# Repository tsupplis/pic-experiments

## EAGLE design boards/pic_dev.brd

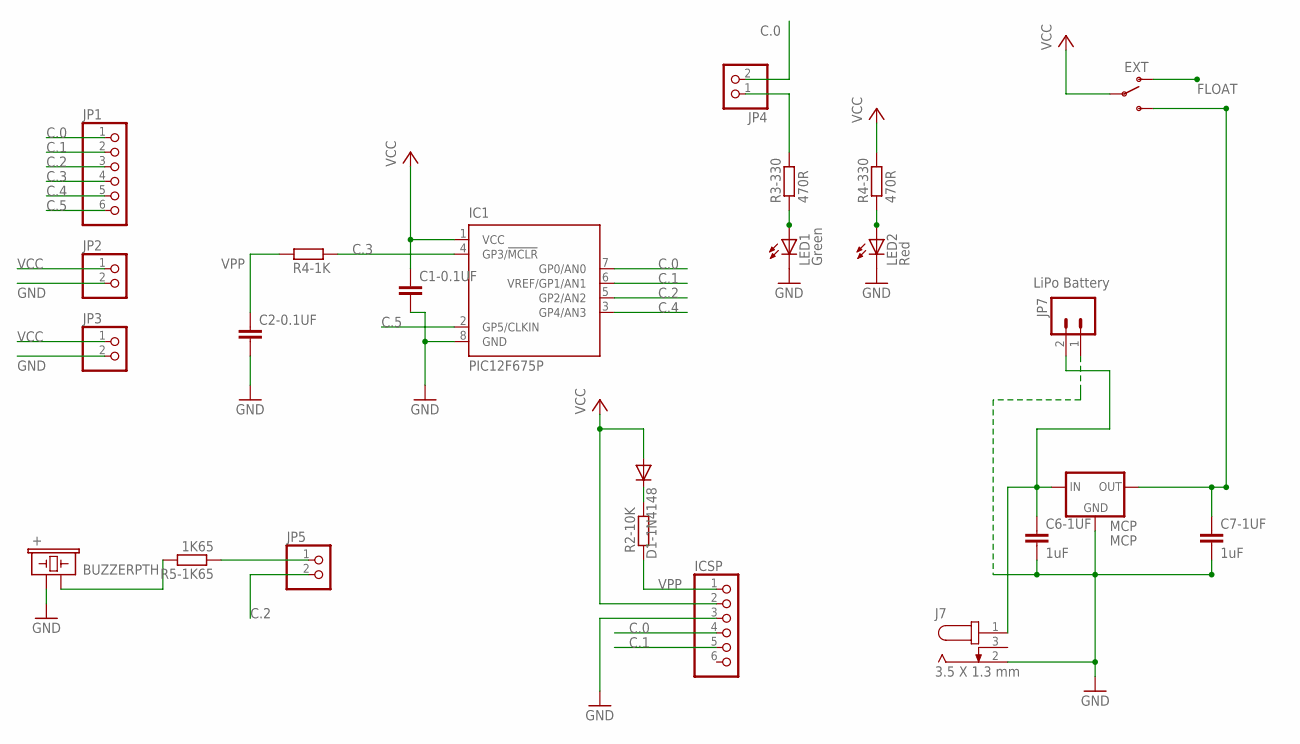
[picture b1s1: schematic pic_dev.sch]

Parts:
+: BUZZERPTH; BUZZER-12MM
C1-0.1UF, C2-0.1UF: C-EU025-025X050; C025-025X050
C6-1UF, C7-1UF: 1uF; C050-025X075
D1-1N4148: 1N4148; DO35-7
IC1: PIC12F675P; DIL8
ICSP: PINHD-1X6; 1X06
J7: 3.5 X 1.3 mm; 3.5X1.3MM_DC_JACK
JP1: PINHD-1X6; 1X06
JP2, JP3, JP4, JP5: PINHD-1X2; 1X02
JP7: LiPo Battery; JST-2-PTH
LED1: Green; LED3MM
LED2: Red; LED3MM
MCP: MCP; TO92-
ON: EXT; SWITCH-SPDT
R2-10K, R4-1K: R-EU_0207/10; 0207/10
R3-330, R4-330: 470R; 0207/10
R5-1K65: 1K65; 0207/10

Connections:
C.0: IC1.7 (GP0/AN0), ICSP.4, JP1.1, JP4.2
C.1: IC1.6 (VREF/GP1/AN1), ICSP.5, JP1.2
C.2: IC1.5 (GP2/AN2), JP1.3, JP5.2
C.3: IC1.4 (GP3/!MCLR), JP1.4, R4-1K.1
C.4: IC1.3 (GP4/AN3), JP1.5
C.5: IC1.2 (GP5/CLKIN), JP1.6
FLOAT: ON.1 (O)
GND: +.+ (1), C1-0.1UF.2, C2-0.1UF.2, C6-1UF.2, C7-1UF.2, IC1.8 (GND), ICSP.3, J7.2, JP2.2, JP3.2, JP7.1, LED1.K (C), LED2.K (C), MCP.3 (GND)
unnamed: LED2.A, R4-330.1
unnamed: +.- (2), R5-1K65.2
unnamed: JP4.1, R3-330.2
unnamed: LED1.A, R3-330.1
unnamed: D1-1N4148.C, R2-10K.2
unnamed: JP5.1, R5-1K65.1
VCC: C1-0.1UF.1, D1-1N4148.A, IC1.1 (VCC), ICSP.2, JP2.1, JP3.1, ON.2, R4-330.2
VCCEXT: C6-1UF.1, J7.1, JP7.2, MCP.2 (IN)
VCCREG: C7-1UF.1, MCP.1 (OUT), ON.3 (S)
VPP: C2-0.1UF.1, ICSP.1, R2-10K.1, R4-1K.2

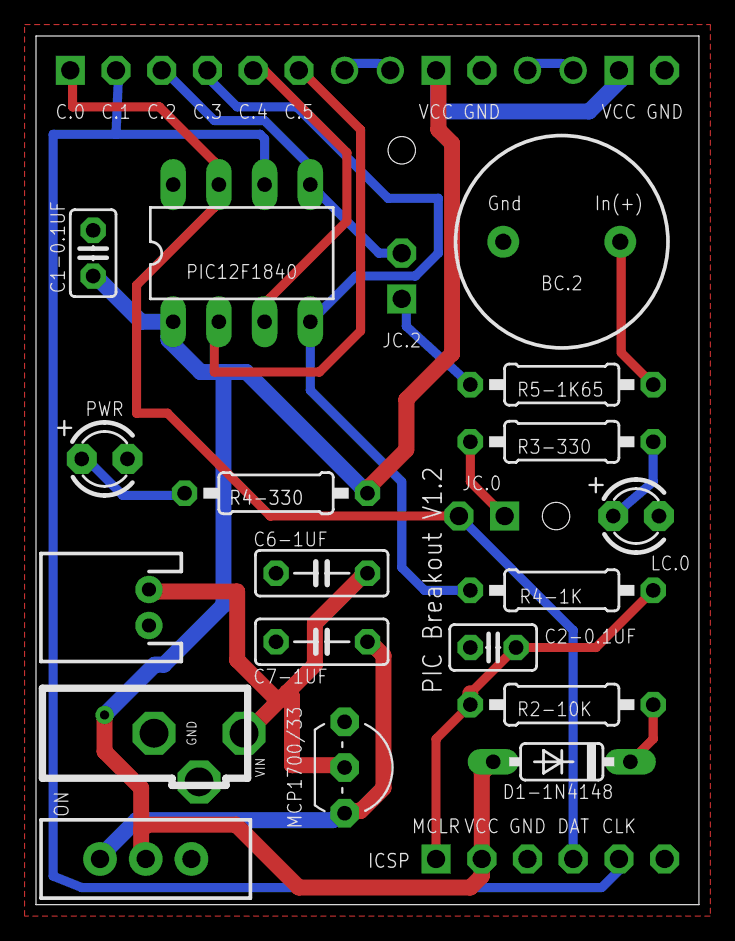
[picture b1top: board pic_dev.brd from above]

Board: 2 copper layers, 36.8 x 48.3 mm, 24 parts (0 on the bottom side), 17 nets.

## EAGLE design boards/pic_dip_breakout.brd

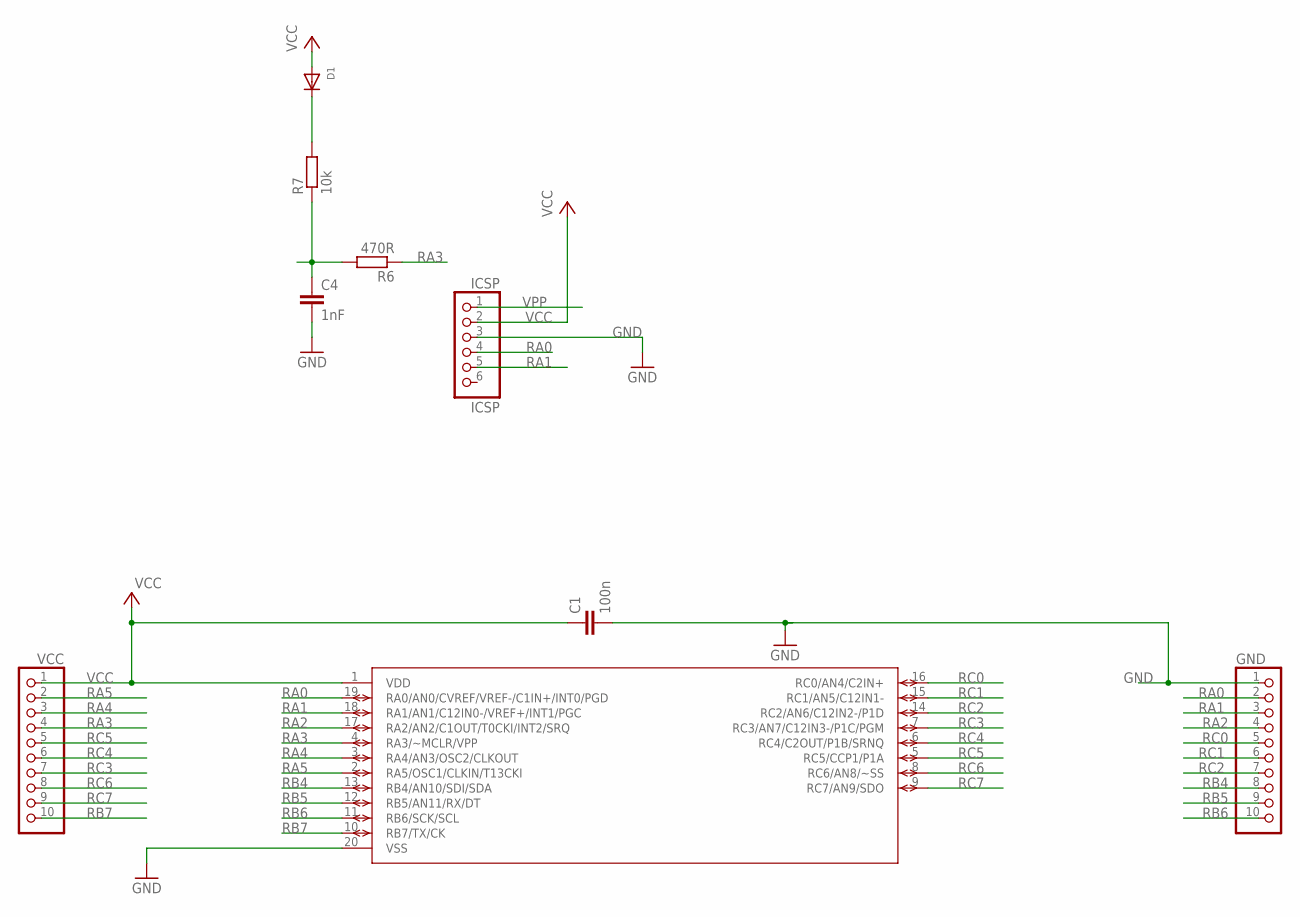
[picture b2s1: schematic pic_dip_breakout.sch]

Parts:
C1: 100n; C0805
C4: 1nF; C0805
D1: DIODESOD-323F; SOD-323F
GND: PH1X10OCT076; PH1X10OCT76
ICSP: ICSP; 1X06
R6: 470R; R0805
R7: 10k; R0805
U$1: PIC18F14K22-I/P; DIP254P762X533-20
VCC: PH1X10OCT076; PH1X10OCT76

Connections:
GND: C1.2, C4.2, GND.1, ICSP.3, U$1.20 (VSS)
unnamed: D1.C, R7.2
RA0: GND.2, ICSP.4, U$1.19 (RA0/AN0/CVREF/VREF-/C1IN+/INT0/PGD)
RA1: GND.3, ICSP.5, U$1.18 (RA1/AN1/C12IN0-/VREF+/INT1/PGC)
RA2: GND.4, U$1.17 (RA2/AN2/C1OUT/T0CKI/INT2/SRQ)
RA3: R6.1, U$1.4 (RA3/~MCLR/VPP), VCC.4
RA4: U$1.3 (RA4/AN3/OSC2/CLKOUT), VCC.3
RA5: U$1.2 (RA5/OSC1/CLKIN/T13CKI), VCC.2
RB4: GND.8, U$1.13 (RB4/AN10/SDI/SDA)
RB5: GND.9, U$1.12 (RB5/AN11/RX/DT)
RB6: GND.10, U$1.11 (RB6/SCK/SCL)
RB7: U$1.10 (RB7/TX/CK), VCC.10
RC0: GND.5, U$1.16 (RC0/AN4/C2IN+)
RC1: GND.6, U$1.15 (RC1/AN5/C12IN1-)
RC2: GND.7, U$1.14 (RC2/AN6/C12IN2-/P1D)
RC3: U$1.7 (RC3/AN7/C12IN3-/P1C/PGM), VCC.7
RC4: U$1.6 (RC4/C2OUT/P1B/SRNQ), VCC.6
RC5: U$1.5 (RC5/CCP1/P1A), VCC.5
RC6: U$1.8 (RC6/AN8/~SS), VCC.8
RC7: U$1.9 (RC7/AN9/SDO), VCC.9
VCC: C1.1, D1.A, ICSP.2, U$1.1 (VDD), VCC.1
VPP: C4.1, ICSP.1, R6.2, R7.1

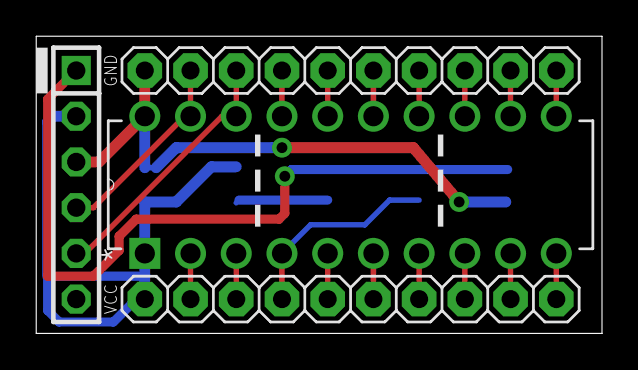
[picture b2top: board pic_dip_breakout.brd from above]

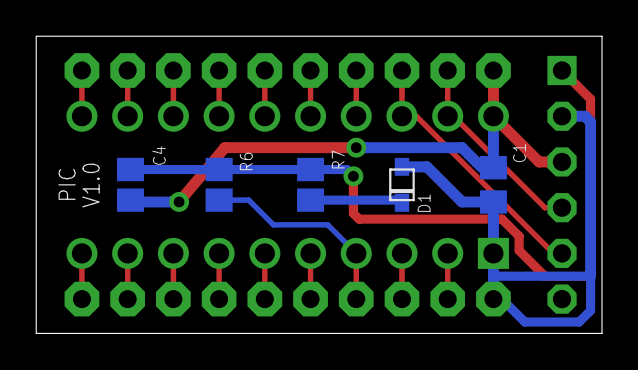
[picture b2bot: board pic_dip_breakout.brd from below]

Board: 2 copper layers, 31.4 x 16.5 mm, 9 parts (5 on the bottom side), 22 nets.

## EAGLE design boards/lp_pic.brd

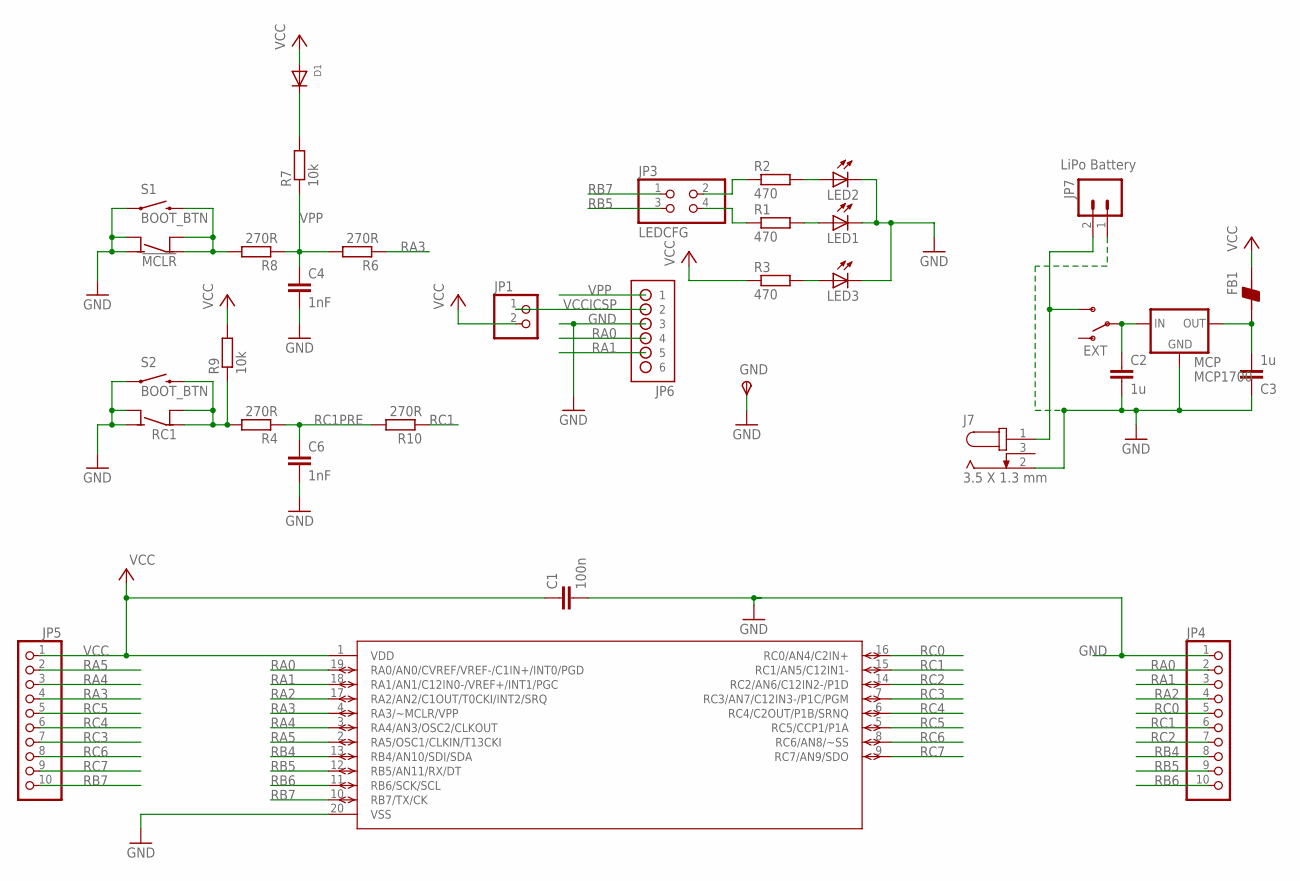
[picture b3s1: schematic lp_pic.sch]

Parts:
!MCLR: !MCLR; 6MMTACTILE_4PIN
C1: 100n; C0805
C2, C3: 1u; C0805
C4, C6: 1nF; C0805
D1: DIODESOD-323F; SOD-323F
FB1: BEAD-0805; 0805
GND: TPSTP20R; TP20R
J7: 3.5 X 1.3 mm; 3.5X1.3MM_DC_JACK
JP1: PINHD-1X2; 1X02
JP3: LEDCFG; 2X02
JP4, JP5: PH1X10OCT076; PH1X10OCT76
JP6: No Load; HDR-1X6_OFFSET
JP7: LiPo Battery; JST-2-PTH
LED1, LED2, LED3: 0; CHIPLED_1206
MCP: MCP1700; SOT-23
ON: EXT; SWITCH-SPDT
R1, R2, R3: 470; R0805
R4, R6, R8, R10: 270R; R0805
R7, R9: 10k; R0805
RC1: RC1; 6MMTACTILE_4PIN
S1, S2: BOOT_BTN; TACTILE-SWITCH-1101NE
U$1: PIC18F14K22-I/P; DIP254P762X533-20

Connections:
GND: !MCLR.A1 (NO), !MCLR.A2 (NO), C1.2, C2.2, C3.1, C4.2, C6.2, GND.TP, J7.2, JP4.1, JP6.3, JP7.1, LED1.C, LED2.C, LED3.C, MCP.1 (GND), RC1.A1 (NO), RC1.A2 (NO), S1.1, S2.1, U$1.20 (VSS)
unnamed: JP3.2, R2.1
unnamed: JP3.4, R1.1
unnamed: C2.1, MCP.3 (IN), ON.2
unnamed: R4.2, R9.1, RC1.B1 (COM), RC1.B2 (COM), S2.2
unnamed: !MCLR.B1 (COM), !MCLR.B2 (COM), R8.2, S1.2
unnamed: C3.2, FB1.1, MCP.2 (OUT)
unnamed: D1.C, R7.2
unnamed: LED3.A, R3.2
unnamed: LED1.A, R1.2
unnamed: LED2.A, R2.2
RA0: JP4.2, JP6.4, U$1.19 (RA0/AN0/CVREF/VREF-/C1IN+/INT0/PGD)
RA1: JP4.3, JP6.5, U$1.18 (RA1/AN1/C12IN0-/VREF+/INT1/PGC)
RA2: JP4.4, U$1.17 (RA2/AN2/C1OUT/T0CKI/INT2/SRQ)
RA3: JP5.4, R6.1, U$1.4 (RA3/~MCLR/VPP)
RA4: JP5.3, U$1.3 (RA4/AN3/OSC2/CLKOUT)
RA5: JP5.2, U$1.2 (RA5/OSC1/CLKIN/T13CKI)
RB4: JP4.8, U$1.13 (RB4/AN10/SDI/SDA)
RB5: JP3.3, JP4.9, U$1.12 (RB5/AN11/RX/DT)
RB6: JP4.10, U$1.11 (RB6/SCK/SCL)
RB7: JP3.1, JP5.10, U$1.10 (RB7/TX/CK)
RC0: JP4.5, U$1.16 (RC0/AN4/C2IN+)
RC1: JP4.6, R10.1, U$1.15 (RC1/AN5/C12IN1-)
RC1PRE: C6.1, R4.1, R10.2
RC2: JP4.7, U$1.14 (RC2/AN6/C12IN2-/P1D)
RC3: JP5.7, U$1.7 (RC3/AN7/C12IN3-/P1C/PGM)
RC4: JP5.6, U$1.6 (RC4/C2OUT/P1B/SRNQ)
RC5: JP5.5, U$1.5 (RC5/CCP1/P1A)
RC6: JP5.8, U$1.8 (RC6/AN8/~SS)
RC7: JP5.9, U$1.9 (RC7/AN9/SDO)
VCC: C1.1, D1.A, FB1.2, JP1.2, JP5.1, R3.1, R9.2, U$1.1 (VDD)
VCCEXT: J7.1, JP7.2, ON.3 (S)
VCCICSP: JP1.1, JP6.2
VPP: C4.1, JP6.1, R6.2, R7.1, R8.1

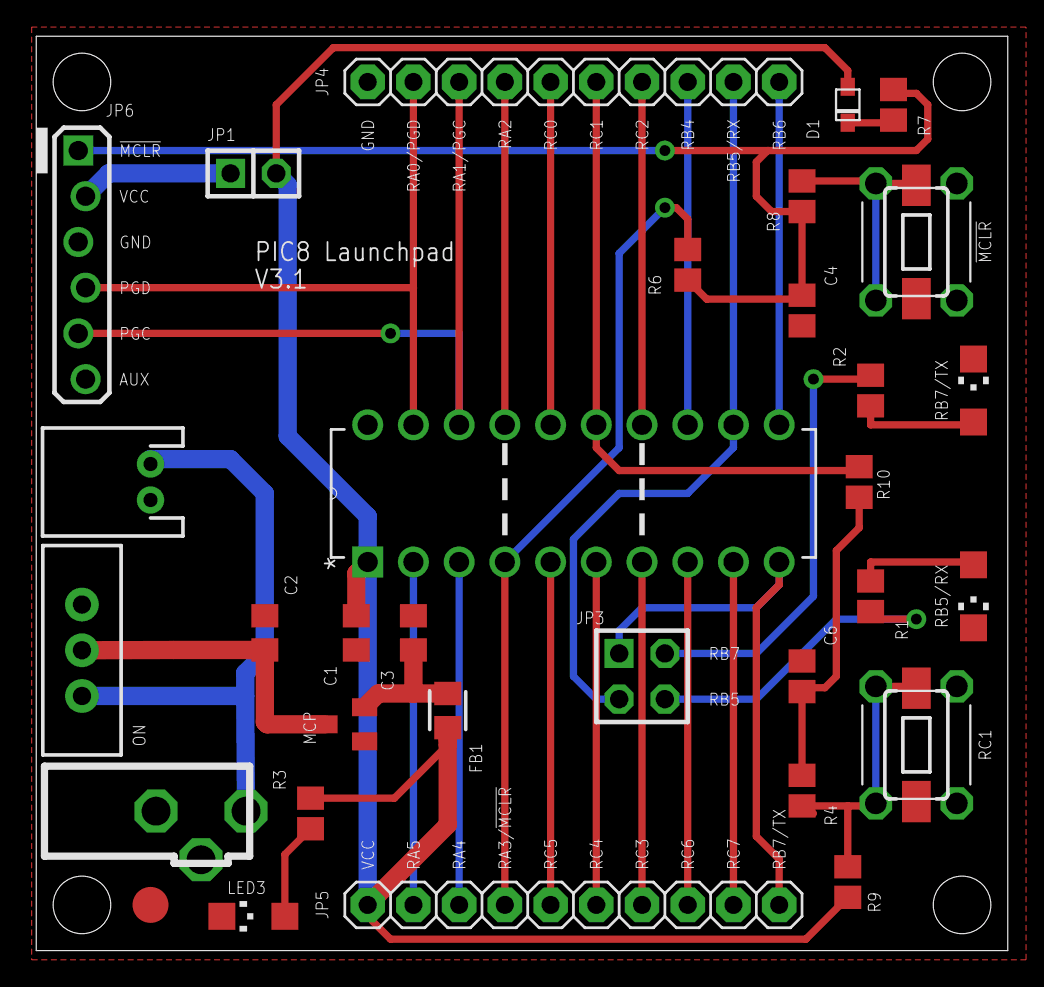
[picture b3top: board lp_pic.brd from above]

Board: 2 copper layers, 54.0 x 50.8 mm, 34 parts (0 on the bottom side), 34 nets.

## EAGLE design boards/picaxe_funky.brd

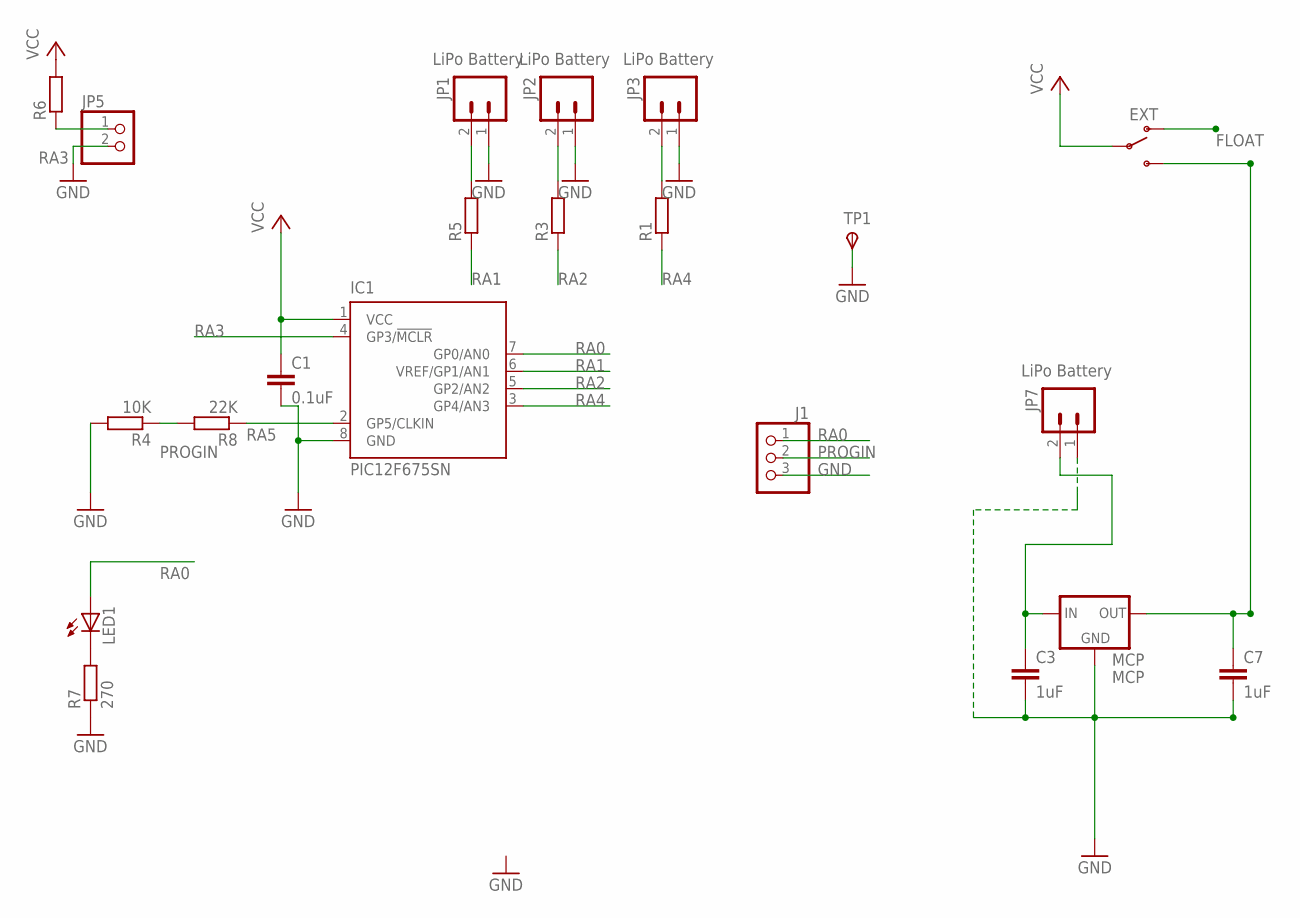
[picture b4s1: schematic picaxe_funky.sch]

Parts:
C1: 0.1uF; C0805
C3, C7: 1uF; C0805
IC1: PIC12F675SN; SO-08
J1: PINHD-1X3; 1X03
JP1, JP2, JP3, JP7: LiPo Battery; JST-2-PTH
JP5: PINHD-1X2; 1X02
LED1: LEDCHIPLED_1206; CHIPLED_1206
MCP: MCP; SOT-23
ON: EXT; SWITCH-SPDT
R1, R3, R5, R6: R-EU_R0805; R0805
R4: 10K; R0805
R7: 270; R0805
R8: 22K; R0805
TP1: TPSTP20R; TP20R

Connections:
FLOAT: ON.1 (O)
GND: C1.2, C3.2, C7.2, IC1.8 (GND), J1.3, JP1.1, JP2.1, JP3.1, JP5.2, JP7.1, MCP.1 (GND), R4.2, R7.1, TP1.TP
unnamed: JP1.2, R5.2
unnamed: JP2.2, R3.2
unnamed: JP3.2, R1.2
unnamed: LED1.C, R7.2
PROGIN: J1.2, R4.1, R8.2
RA0: IC1.7 (GP0/AN0), J1.1, LED1.A
RA1: IC1.6 (VREF/GP1/AN1), R5.1
RA2: IC1.5 (GP2/AN2), R3.1
RA3: IC1.4 (GP3/!MCLR), JP5.1, R6.1
RA4: IC1.3 (GP4/AN3), R1.1
RA5: IC1.2 (GP5/CLKIN), R8.1
VCC: C1.1, IC1.1 (VCC), ON.2, R6.2
VCCEXT: C3.1, JP7.2, MCP.3 (IN)
VCCREG: C7.1, MCP.2 (OUT), ON.3 (S)

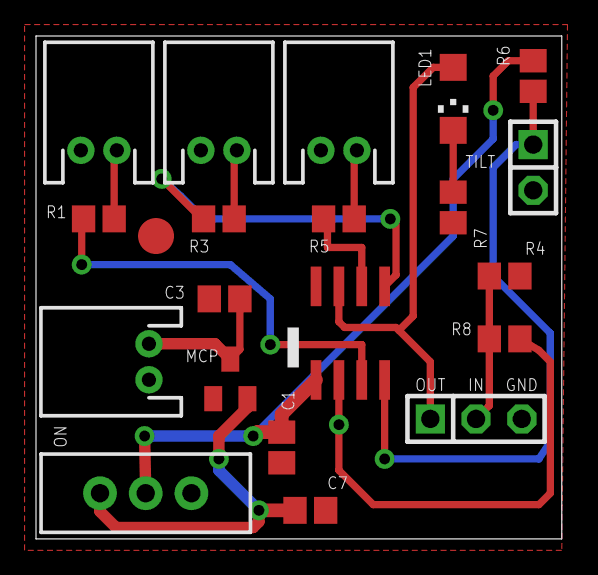
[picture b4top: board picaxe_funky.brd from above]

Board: 2 copper layers, 29.2 x 27.9 mm, 21 parts (0 on the bottom side), 15 nets.

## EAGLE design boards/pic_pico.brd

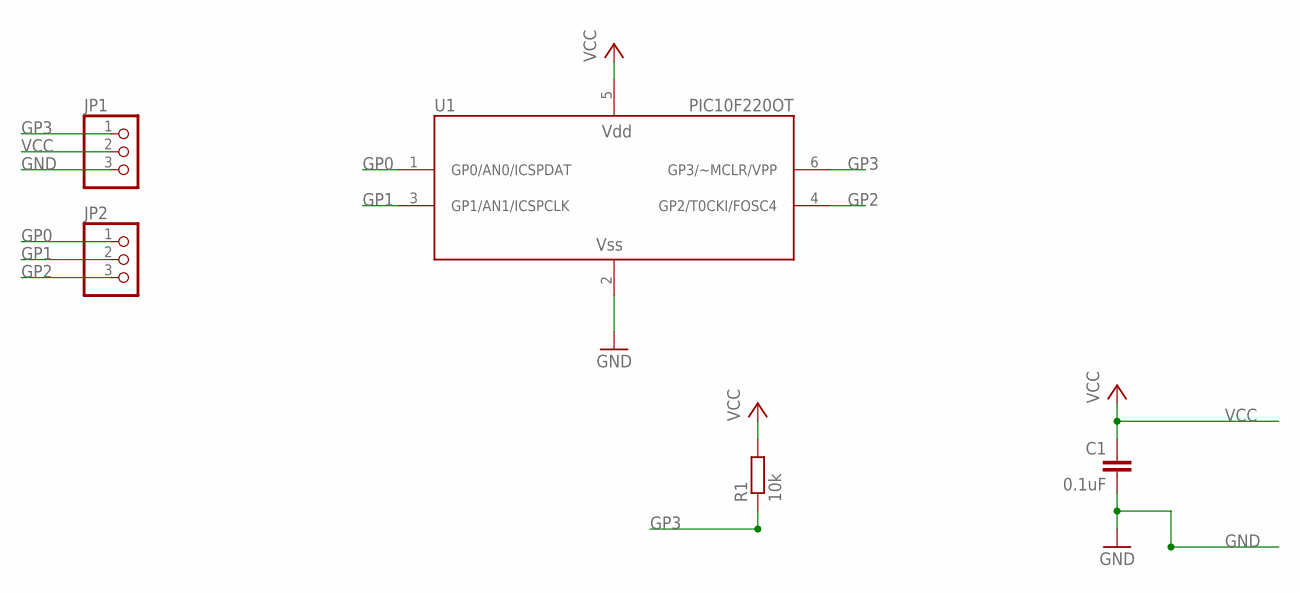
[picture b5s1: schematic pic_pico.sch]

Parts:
C1: 0.1uF; C0603
JP1, JP2: PINHD-1X3; 1X03
R1: 10k; R0603
U1: PIC10F220OT; SOT-23-6

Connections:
GND: C1.2, JP1.3, U1.2 (VSS)
GP0: JP2.1, U1.1 (GP0/AN0/ICSPDAT)
GP1: JP2.2, U1.3 (GP1/AN1/ICSPCLK)
GP2: JP2.3, U1.4 (GP2/T0CKI/FOSC4)
GP3: JP1.1, R1.1, U1.6 (GP3/~MCLR/VPP)
VCC: C1.1, JP1.2, R1.2, U1.5 (VDD)

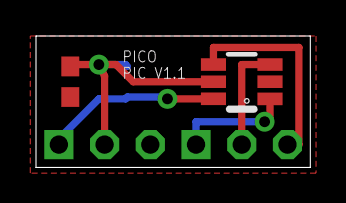
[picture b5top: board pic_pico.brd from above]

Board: 2 copper layers, 15.2 x 7.3 mm, 5 parts (1 on the bottom side), 6 nets.

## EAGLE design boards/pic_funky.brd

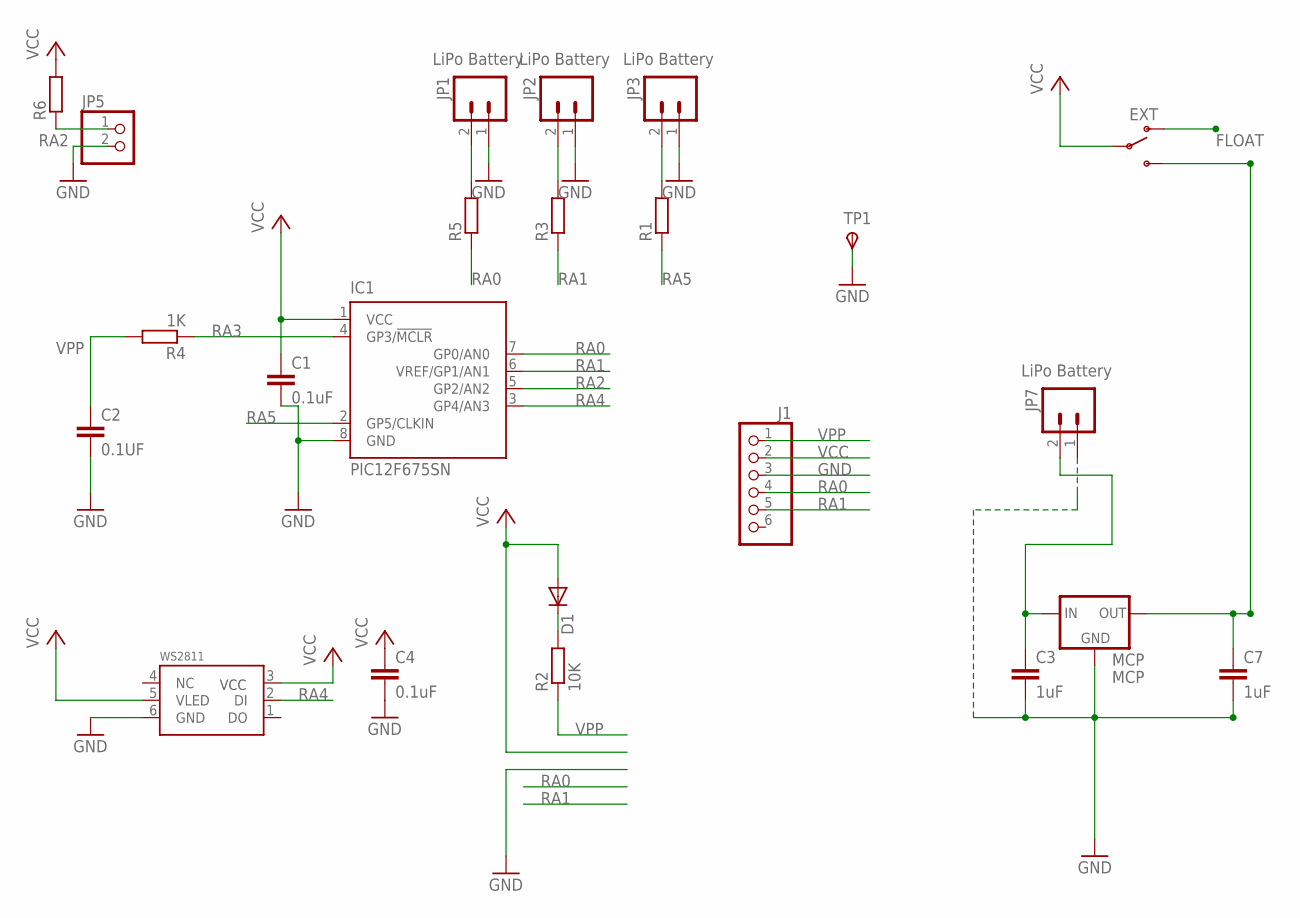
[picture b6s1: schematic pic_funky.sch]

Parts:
C1, C4: 0.1uF; C0805
C2: 0.1UF; C0805
C3, C7: 1uF; C0805
D1: 1N4148; SOD-323F
IC1: PIC12F675SN; SO-08
J1: PH1X650MIL; PH1X6_50MIL
JP1, JP2, JP3, JP7: LiPo Battery; JST-2-PTH
JP5: PINHD-1X2; 1X02
MCP: MCP; SOT-23
ON: EXT; SWITCH-SPDT
R1, R3, R5, R6: R-EU_R0805; R0805
R2: 10K; R0805
R4: 1K; R0805
TP1: TPSTP20R; TP20R
WS2811: 5050WS2811W; RGBLED5050W

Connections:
FLOAT: ON.1 (O)
GND: C1.2, C2.2, C3.2, C4.2, C7.2, IC1.8 (GND), J1.3, JP1.1, JP2.1, JP3.1, JP5.2, JP7.1, MCP.1 (GND), TP1.TP, WS2811.6 (GND)
unnamed: JP1.2, R5.2
unnamed: JP2.2, R3.2
unnamed: JP3.2, R1.2
unnamed: D1.C, R2.2
RA0: IC1.7 (GP0/AN0), J1.4, R5.1
RA1: IC1.6 (VREF/GP1/AN1), J1.5, R3.1
RA2: IC1.5 (GP2/AN2), JP5.1, R6.1
RA3: IC1.4 (GP3/!MCLR), R4.1
RA4: IC1.3 (GP4/AN3), WS2811.2 (DI)
RA5: IC1.2 (GP5/CLKIN), R1.1
VCC: C1.1, C4.1, D1.A, IC1.1 (VCC), J1.2, ON.2, R6.2, WS2811.3 (VCC), WS2811.5 (VLED)
VCCEXT: C3.1, JP7.2, MCP.3 (IN)
VCCREG: C7.1, MCP.2 (OUT), ON.3 (S)
VPP: C2.1, J1.1, R2.1, R4.2

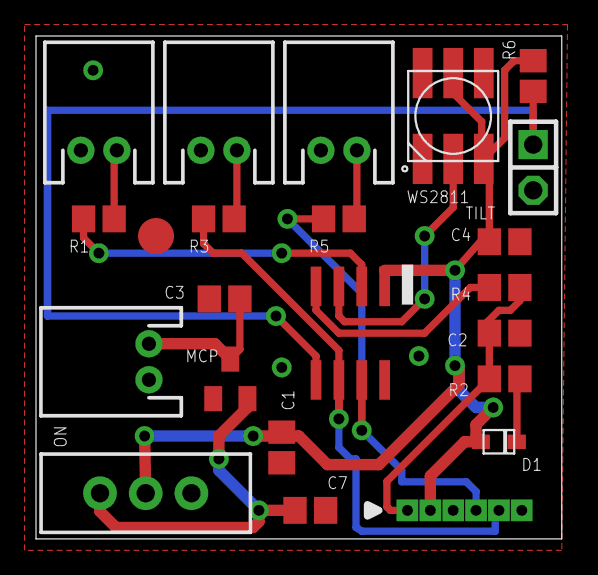
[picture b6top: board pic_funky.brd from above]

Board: 2 copper layers, 29.2 x 27.9 mm, 23 parts (0 on the bottom side), 15 nets.

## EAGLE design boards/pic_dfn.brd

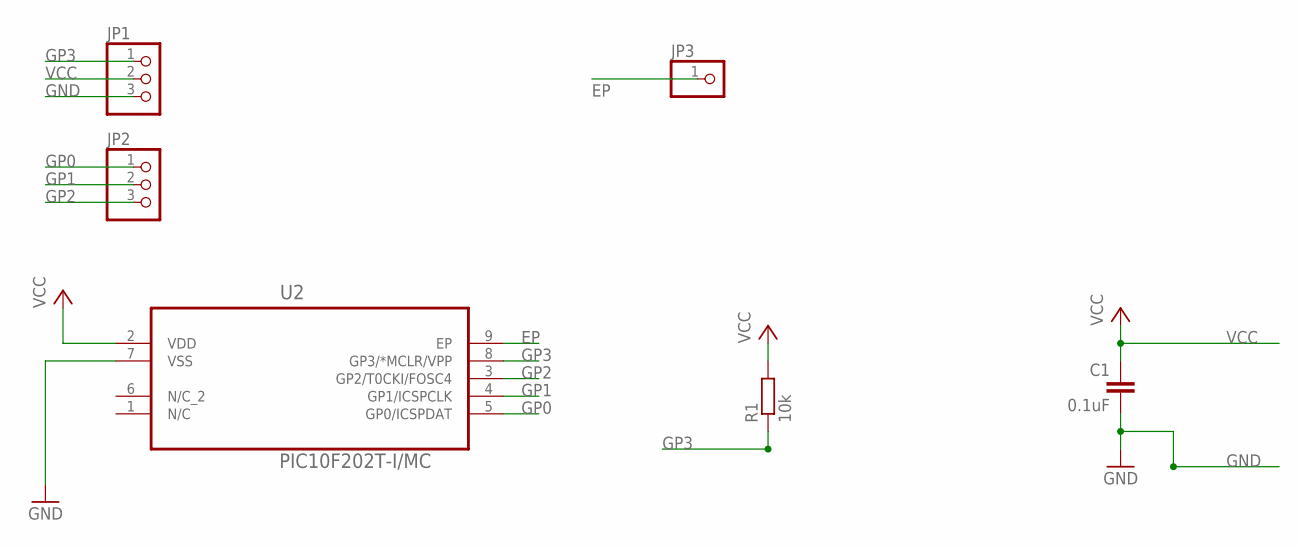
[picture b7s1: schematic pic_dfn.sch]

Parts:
C1: 0.1uF; C0603
JP1, JP2: PINHD-1X3; 1X03
JP3: PINHD-1X1; 1X01
R1: 10k; R0603
U2: PIC10F202T-I/MC; DFN200X300X100-9N

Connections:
EP: JP3.1, U2.9 (EP)
GND: C1.2, JP1.3, U2.7 (VSS)
GP0: JP2.1, U2.5 (GP0/ICSPDAT)
GP1: JP2.2, U2.4 (GP1/ICSPCLK)
GP2: JP2.3, U2.3 (GP2/T0CKI/FOSC4)
GP3: JP1.1, R1.1, U2.8 (GP3/*MCLR/VPP)
VCC: C1.1, JP1.2, R1.2, U2.2 (VDD)

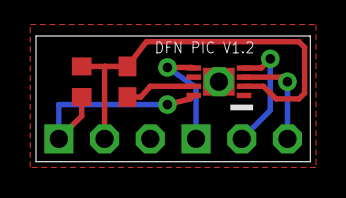
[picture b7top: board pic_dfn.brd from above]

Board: 2 copper layers, 15.2 x 7.0 mm, 6 parts (1 on the bottom side), 7 nets.

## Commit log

2016-04-05 Initial Content

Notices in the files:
parts and their libraries:
SparkFun: Licensing: CC v3.0 Share-Alike You are welcome to use this library for commercial purposes.
SparkFun-Electromechanical: Licensing: Creative Commons ShareAlike 4.0 International - https://creativecommons.org/licenses/by-sa/4.0
